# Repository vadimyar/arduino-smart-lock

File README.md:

# 🚪 Умный дверной замок на Arduino Nano

**Автономная система управления дверным замком с психоакустической индикацией и интеллектуальным контролем доступа**

Проект разработан с упором на надежность, использование свободного ПО (Linux, Arduino IDE) и комфорт пользователей.

---

## ✨ Особенности проекта

### 🔇 Психоакустический "тихий режим"
Вместо стандартного пронзительного писка используется алгоритм **сверхкоротких импульсов** (микросекундные задержки), превращающий звук активного зуммера в мягкий, интеллигентный "щелчок" (в стиле счетчика Гейгера из Half-Life).

### 🎵 Динамическая мелодия удержания
При удержании двери в открытом состоянии система подает сигналы с **ускоряющимся ритмом**. Интервалы между сигналами рассчитываются по формуле **геометрической прогрессии** (закон Вебера-Фехнера), что интуитивно воспринимается человеком как нарастающее "предупреждение о скором закрытии".

###  Двухуровневая система тревоги
Если замок двери остается разблокированным слишком долго:
1. Включается **звуковая сирена** и мигание светодиода
2. Через заданное время **звук автоматически отключается** (чтобы не беспокоить)
3. **Визуальная LED-индикация** продолжает работать до момента блокирования замка двери

### ⚙️ Настраиваемая громкость
3 уровня громкости "щелчков", выбираемые через сервисную кнопку и сохраняемые в EEPROM.

### 🛡️ Аппаратная надежность
- Использование **watchdog-таймера (WDT)**
- Защита от дребезга контактов (debounce)
- Корректное управление питанием сервопривода (отключение после движения)

---

## 🔧 Используемые компоненты

| Компонент | Назначение |
|-----------|------------|
| **Arduino Nano** (ATmega328P) | Микроконтроллер |
| **Сервопривод** (SG90/MG995) | Механическое открытие/закрытие |
| **Датчик Холла** | Определение положения ригеля |
| **Сканер отпечатков пальцев** (К202+R503) | Контроль доступа |
| **Wi-Fi модуль** | Управление замком из УД с Алисой |
| **Активный зуммер** | Звуковая индикация |
| **LED индикаторы** | Визуальная индикация состояния |
| **Кнопки/сканеры** | Триггеры открытия (активный низкий уровень) |

---

## 📐 Схема подключения

| Компонент | Пин Arduino | Примечание |
|-----------|-------------|------------|
| Сервопривод | D10 | PWM |
| Зуммер | D9 | PWM (режим быстрых импульсов) |
| Датчик Холла | D6 | INPUT_PULLUP, активный низкий |
| Сервисная кнопка | D4 | INPUT_PULLUP, настройка громкости |
| Триггеры открытия | D2, D3, D5 | INPUT_PULLUP |
| LED индикации | D8, D11, D13 | D11 - PWM (режим "дыхание" подсветки) |

---

## 🚀 Установка и настройка

### 1. Прошивка
Загрузите код `door_lock.ino` с помощью **Arduino IDE** или **PlatformIO**.

### 2. Настройка громкости
- **Удерживайте** сервисную кнопку (D4) более **1.5 секунды** → вход в режим настройки
- **Коротко нажимайте** кнопку для переключения между 3 уровнями громкости
- **Удерживайте** кнопку 1.5 секунды → сохранение в EEPROM и выход

### 3. Основные параметры
В начале файла `door_lock.ino` можно изменить:

```cpp
const unsigned long HOLD_TIME = 10000;        // Время удержания (мс)
const byte HOLD_TICK_COUNT = 30;              // Количество тиков
const unsigned long ALARM_DELAY = 15000;      // Задержка до тревоги (мс)
const unsigned long ALARM_SOUND_DURATION = 15000; // Длительность звука тревоги (мс)

```

### 🤝 Вклад в проект
Проект создан с любовью к свободному ПО и точным наукам. Если у вас есть идеи по улучшению кода, оптимизации или новые идеи для мелодий — Pull Request'ы приветствуются!

### 📜 Лицензия
Этот проект распространяется под лицензией MIT License — используйте freely в любых целях.

### 👨‍💻 Автор
**Vadimyar** — физик, энтузиаст Linux и свободного ПО, разработчик образовательных проектов на Arduino/ESP.

> *"Замок должен быть не только надежным, но и интеллигентным"*

<br>

<div align="center">

Сделано с ❤️ на Arduino и Linux
[⬆️ В начало](#top)

</div>

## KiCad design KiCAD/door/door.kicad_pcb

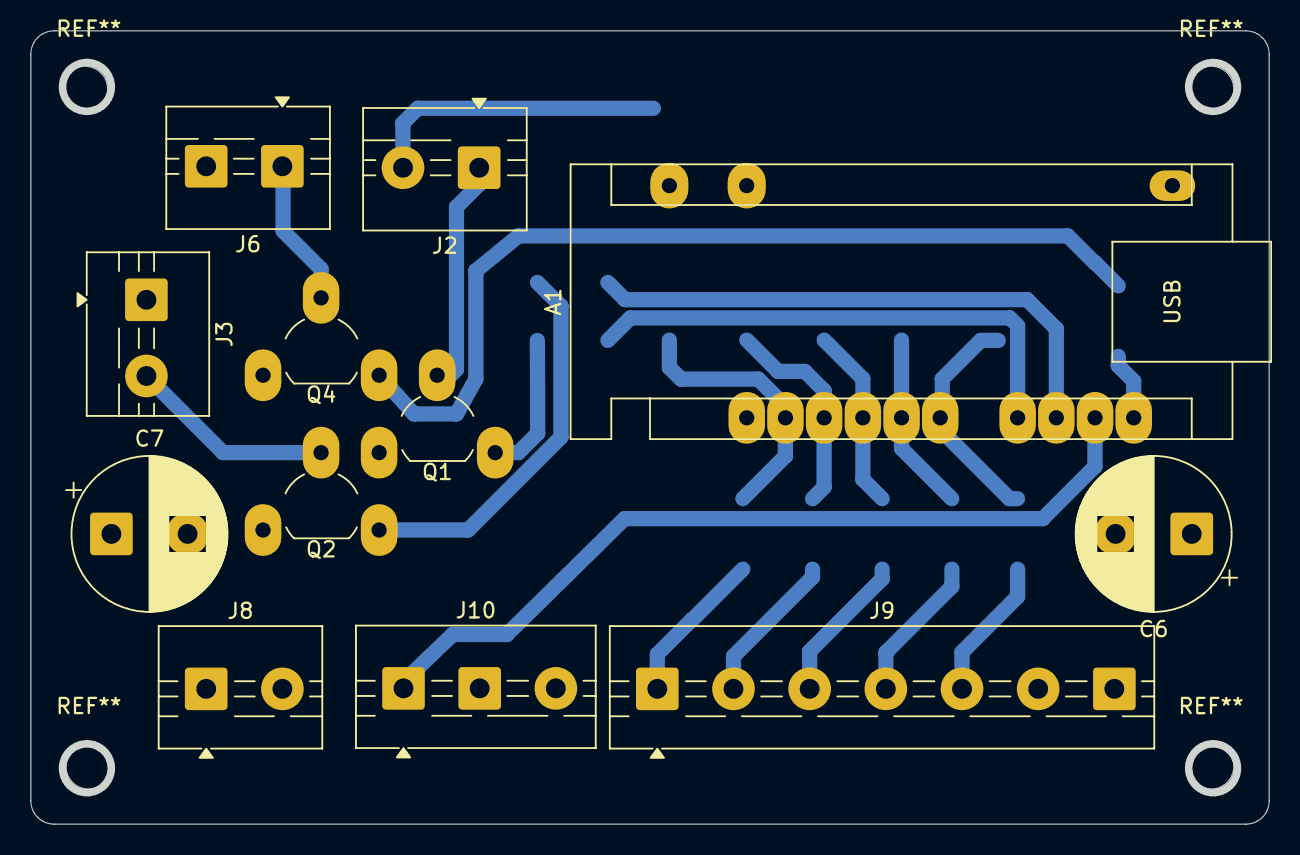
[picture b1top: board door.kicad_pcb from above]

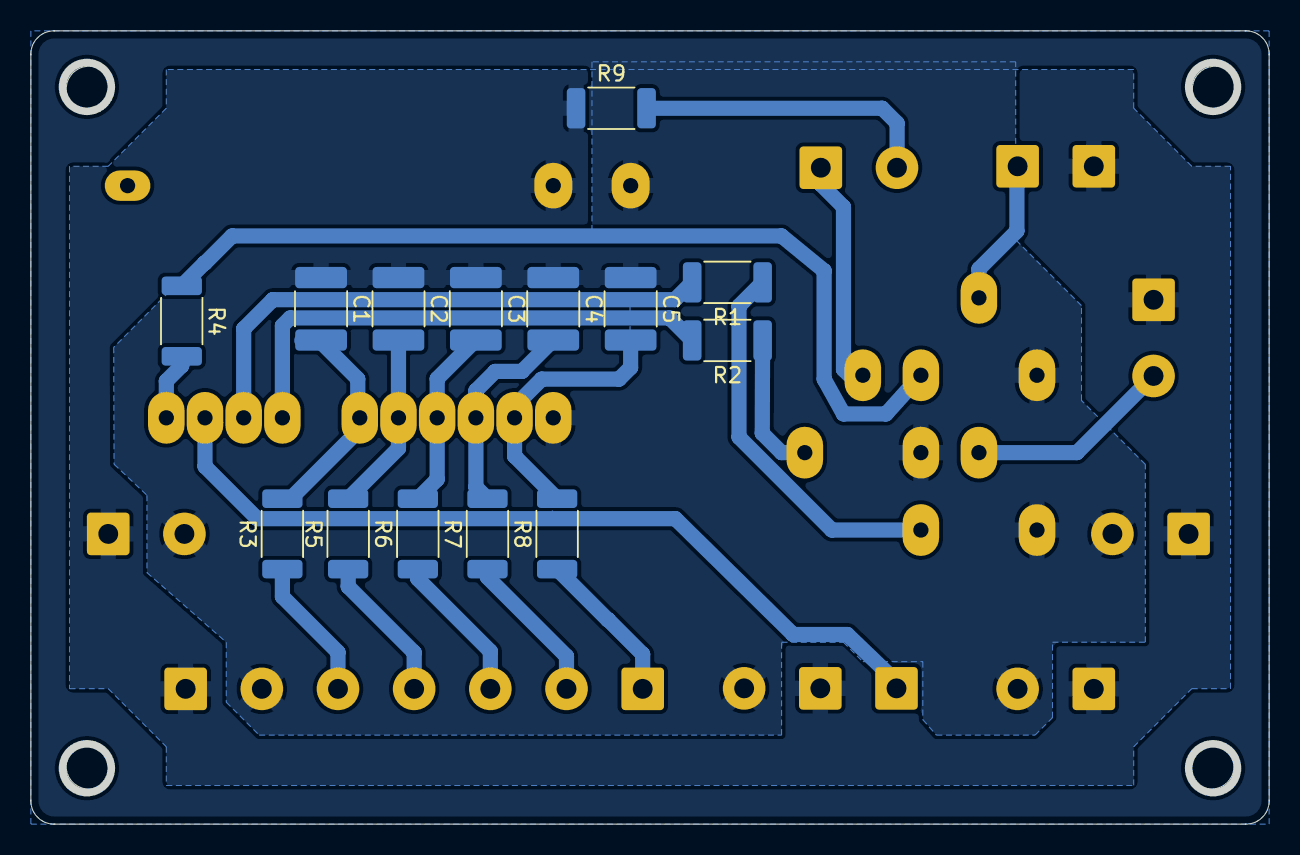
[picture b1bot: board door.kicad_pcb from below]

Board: 2 copper layers, 81.3 x 52.1 mm, 26 parts (14 on the bottom side), 23 nets.

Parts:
A1: Arduino_Nano_v3.x; Arduino_Nano
C1, C2, C3, C4, C5: 100nf; C_1812_4532Metric
C6, C7: 1.5mf; CP_Radial_D10.0mm_P5.00mm
J2, J3, J6, J8: Screw_Terminal_01x02; TerminalBlock_MaiXu_MX126-5.0-02P_1x02_P5.00mm
J9: Screw_Terminal_01x04; TerminalBlock_MaiXu_MX126-5.0-07P_1x07_P5.00mm
J10: Screw_Terminal_01x03; TerminalBlock_MaiXu_MX126-5.0-03P_1x03_P5.00mm
Q1, Q2, Q4: PN2222A; TO-92_SuperWide
R1, R2, R3, R4, R5, R6, R7, R8: 1k; R_2010_5025Metric
R9: 270; R_2010_5025Metric

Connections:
+5V: A1.27 (+5V), C6.1, C7.1, J3.1, J6.2, J8.1, J9.7, J10.2, R9.1
GND: A1.4 (GND), A1.29 (GND), C1.1, C2.1, C3.1, C4.1, C5.1, C6.2, C7.2, J8.2, J9.6, J10.3, Q1.1 (E), Q2.1 (E), Q4.1 (E)
unnamed: A1.5 (D2), C5.2, R8.2
unnamed: A1.6 (D3), C4.2, R7.2
unnamed: A1.7 (D4), C3.2, R6.2
unnamed: A1.8 (D5), C2.2, R5.2
unnamed: A1.9 (D6), C1.2, R3.2
unnamed: A1.11 (D8), R2.2
unnamed: A1.12 (D9), R1.2
unnamed: A1.13 (D10), J10.1
unnamed: A1.14 (D11), R4.2
unnamed: J2.1, Q1.2 (C)
unnamed: J2.2, R9.2
unnamed: J3.2, Q2.2 (C)
unnamed: J6.1, Q4.2 (C)
unnamed: J9.1, R8.1
unnamed: J9.2, R7.1
unnamed: J9.3, R6.1
unnamed: J9.4, R5.1
unnamed: J9.5, R3.1
unnamed: Q1.3 (B), R2.1
unnamed: Q2.3 (B), R1.1
unnamed: Q4.3 (B), R4.1
